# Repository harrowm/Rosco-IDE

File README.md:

# Rosco-IDE
A simple IDE interface for the rosco sbc based on the work of Mark Murray

This is arhcived .. the footprint for the ATF1508 is not correct .. do not attempt ot use!

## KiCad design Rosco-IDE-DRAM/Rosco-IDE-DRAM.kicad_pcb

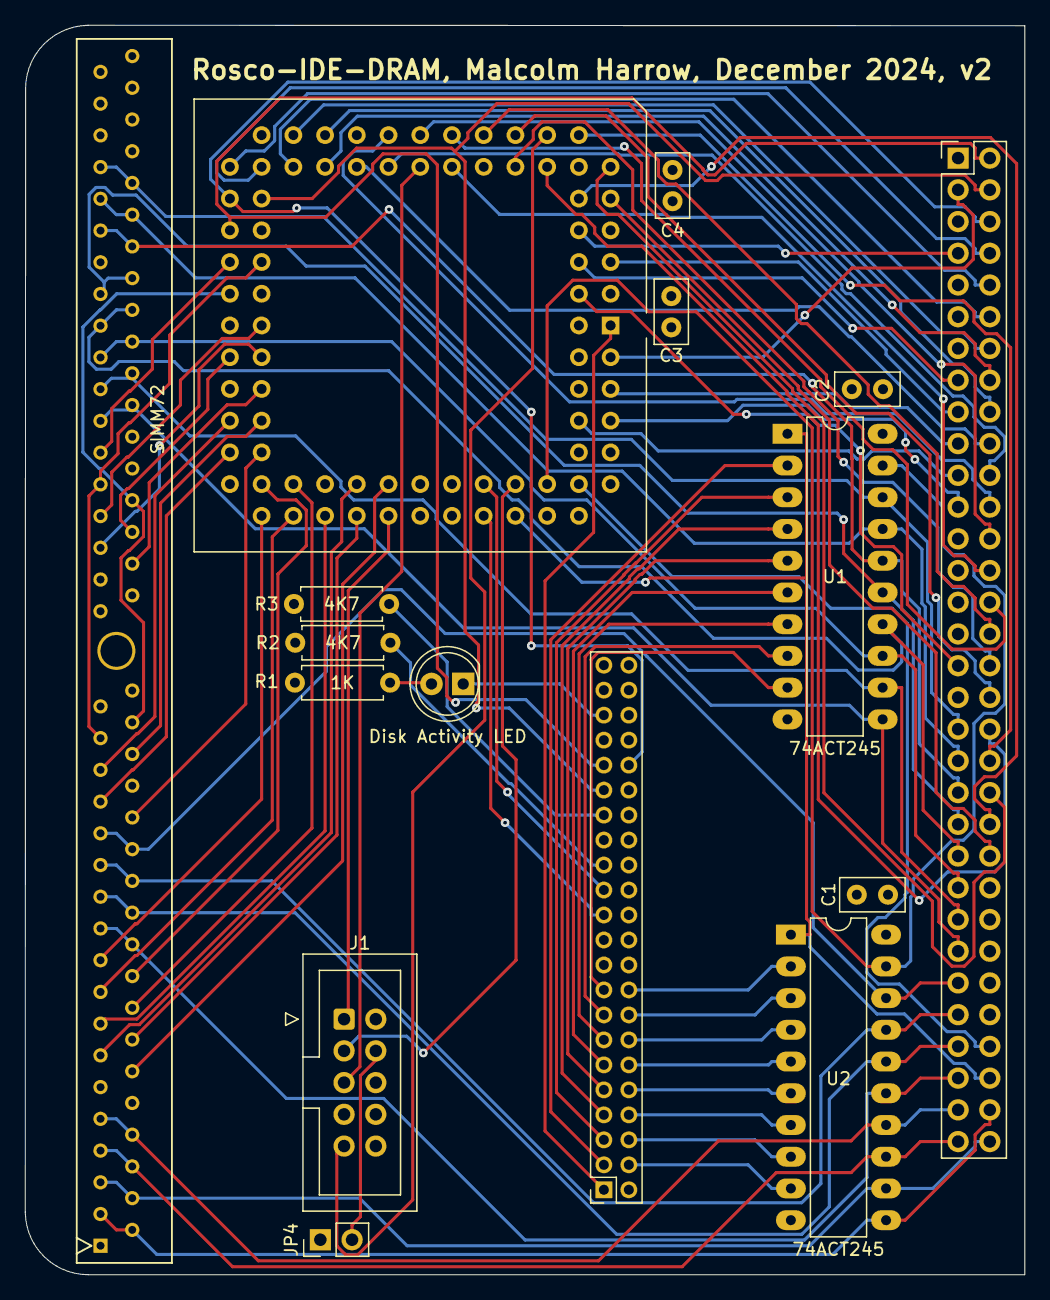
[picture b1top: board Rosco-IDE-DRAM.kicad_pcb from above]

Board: 4 copper layers, 80.0 x 100.0 mm, 16 parts (0 on the bottom side), 99 nets.

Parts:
BUS1: Conn_02x32_Odd_Even; PinHeader_2x32_P2.54mm_Vertical
C1, C2, C3, C4: 100nF; C_Disc_D5.0mm_W2.5mm_P2.50mm
D1: Disk Activity LED; LED_D5.0mm
J1: Conn_02x05_Odd_Even; IDC-Header_2x05_P2.54mm_Vertical
J2: Conn_02x22_Odd_Even; PinSocket_2x22_P2.00mm_Vertical
JP4: Jumper_2_Bridged; PinHeader_1x02_P2.54mm_Vertical
R1: 1K; R_Axial_DIN0207_L6.3mm_D2.5mm_P7.62mm_Horizontal
R2, R3: 4K7; R_Axial_DIN0207_L6.3mm_D2.5mm_P7.62mm_Horizontal
SIMM72: SIMM72
U1, U2: 74ACT245; DIP-20_W7.62mm_LongPads
U3: ATF1504; PLCC-84_THT-Socket

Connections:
+5V: BUS1.1, C1.1, C2.1, C3.1, C4.1, J2.41, JP4.1 (A), R1.1, SIMM72.10 (VCC), SIMM72.30 (VCC), SIMM72.59 (VCC), U1.20 (VCC), U2.20 (VCC), U3.3 (VCCINT), U3.13 (VCCIO), U3.26 (VCCIO), U3.38 (VCCIO), U3.43 (VCCINT), U3.53 (VCCIO), U3.66 (VCCIO), U3.78 (VCCIO)
A1: BUS1.2, J2.35, U3.37 (I/O)
A2: BUS1.4, J2.33, U3.36 (I/O)
A3: BUS1.6, J2.36, U3.35 (I/O)
A4: BUS1.8, U3.34 (I/O)
A5: BUS1.10, U3.33 (I/O)
A6: BUS1.12, U3.31 (I/O)
A7: BUS1.14, U3.30 (I/O)
A8: BUS1.16, U3.29 (I/O)
A9: BUS1.18, U3.28 (I/O)
A10: BUS1.20, U3.27 (I/O)
A11: BUS1.22, U3.25 (I/O)
A12: BUS1.24, U3.24 (I/O)
A13: BUS1.26, U3.22 (I/O)
A14: BUS1.28, U3.21 (I/O)
A15: BUS1.30, U3.20 (PD1/I/O)
A16: BUS1.32, U3.18 (I/O)
A17: BUS1.34, U3.17 (I/O)
A18: BUS1.36, U3.16 (I/O)
A19: BUS1.38, U3.15 (I/O)
A20: BUS1.40, U3.12 (I/O)
A21: BUS1.42, U3.11 (I/O)
A22: BUS1.44, U3.10 (I/O)
A23: BUS1.46, U3.9 (I/O)
BD0: J2.17, U1.9 (A7)
BD1: J2.15, U1.8 (A6)
BD2: J2.13, U1.7 (A5)
BD3: J2.11, U1.6 (A4)
BD4: J2.9, U1.5 (A3)
BD5: J2.7, U1.4 (A2)
BD6: J2.5, U1.3 (A1)
BD7: J2.3, U1.2 (A0)
BD8: J2.4, U2.9 (A7)
BD9: J2.6, U2.8 (A6)
BD10: J2.8, U2.7 (A5)
BD11: J2.10, U2.6 (A4)
BD12: J2.12, U2.5 (A3)
BD13: J2.14, U2.4 (A2)
BD14: J2.16, U2.3 (A1)
BD15: J2.18, U2.2 (A0)
CPUCLK: BUS1.3, U3.83 (GCLK1/I)
D0: BUS1.62, SIMM72.2 (DQ0), SIMM72.3 (DQ16), U2.11 (B7)
D1: BUS1.64, SIMM72.4 (DQ1), SIMM72.5 (DQ17), U2.12 (B6)
D2: BUS1.63, SIMM72.6 (DQ2), SIMM72.7 (DQ18), U2.13 (B5)
D3: BUS1.61, SIMM72.8 (DQ3), SIMM72.9 (DQ19), U2.14 (B4)
D4: BUS1.59, SIMM72.20 (DQ4), SIMM72.21 (DQ20), U2.15 (B3)
D5: BUS1.57, SIMM72.22 (DQ5), SIMM72.23 (DQ21), U2.16 (B2)
D6: BUS1.55, SIMM72.24 (DQ6), SIMM72.25 (DQ22), U2.17 (B1)
D7: BUS1.53, SIMM72.26 (DQ7), SIMM72.27 (DQ23), U2.18 (B0)
D8: BUS1.51, SIMM72.49 (DQ8), SIMM72.50 (DQ24), U1.11 (B7)
D9: BUS1.49, SIMM72.51 (DQ9), SIMM72.52 (DQ25), U1.12 (B6)
D10: BUS1.47, SIMM72.53 (DQ10), SIMM72.54 (DQ26), U1.13 (B5)
D11: BUS1.45, SIMM72.55 (DQ11), SIMM72.56 (DQ27), U1.14 (B4)
D12: BUS1.43, SIMM72.57 (DQ12), SIMM72.58 (DQ28), U1.15 (B3)
D13: BUS1.41, SIMM72.60 (DQ29), SIMM72.61 (DQ13), U1.16 (B2)
D14: BUS1.39, SIMM72.62 (DQ30), SIMM72.63 (DQ14), U1.17 (B1)
D15: BUS1.37, SIMM72.64 (DQ31), SIMM72.65 (DQ15), U1.18 (B0)
DTACK: BUS1.58, U3.76 (I/O)
EXPSEL: BUS1.17, U3.5 (I/O)
FC0: BUS1.19, U3.81 (GCLK3/I/O)
FC1: BUS1.21, U3.80 (I/O)
FC2: BUS1.23, U3.79 (I/O)
GND: BUS1.5, C1.2, C2.2, C3.2, C4.2, J1.2, J1.10, J2.2, J2.19, J2.22, J2.24, J2.26, J2.30, J2.40, J2.43, R2.2, R3.2, SIMM72.1 (GND), SIMM72.39 (GND), SIMM72.72 (GND), U1.10 (GND), U2.10 (GND), U3.7 (GND), U3.19 (GND), U3.32 (GND), U3.42 (GND), U3.47 (GND), U3.59 (GND), U3.72 (GND), U3.82 (GND)
IDEBUF: U1.19 (CE), U2.19 (CE), U3.73 (I/O)
INTRQ: J2.31, R3.1
IOSEL: BUS1.15, U3.6 (I/O)
MA0: SIMM72.12 (A0), U3.63 (I/O)
MA1: SIMM72.13 (A1), U3.61 (I/O)
MA2: SIMM72.14 (A2), U3.60 (I/O)
MA3: SIMM72.15 (A3), U3.58 (I/O)
MA4: SIMM72.16 (A4), U3.57 (I/O)
MA5: SIMM72.17 (A5), U3.56 (I/O)
MA6: SIMM72.18 (A6), U3.55 (I/O)
MA7: SIMM72.28 (A7), U3.52 (I/O)
MA8: SIMM72.31 (A8), U3.49 (I/O)
MA9: SIMM72.32 (A9), U3.50 (I/O)
MA10: SIMM72.19 (A10), U3.54 (I/O)
MA11: SIMM72.29 (A11), U3.51 (I/O)
unnamed: D1.2 (A), R1.2
unnamed: J1.4, JP4.2 (B)
unnamed: J2.27, R2.1
RW: BUS1.60, U1.1 (A->B), U2.1 (A->B), U3.70 (I/O)
TCK: J1.1, U3.62 (TCK/I/O)
TDI: J1.9, U3.14 (TDI/I/O)
TDO: J1.3, U3.71 (TDO/I/O)
TMS: J1.5, U3.23 (TMS/I/O)
UDS: BUS1.33, U3.4 (I/O)
VPA: BUS1.7, U3.8 (I/O)
~CAS0: SIMM72.40 (~CAS0), U3.48 (I/O)
~CAS1: SIMM72.43 (~CAS1), U3.44 (I/O)
~CAS2: SIMM72.41 (~CAS2), U3.46 (I/O/PD2)
~CAS3: SIMM72.42 (~CAS3), U3.45 (I/O)
~DASP: D1.1 (K), J2.39
~IDERD: J2.25, U3.69 (I/O)
~IDEWR: J2.23, U3.68 (I/O)
~MWE: SIMM72.47 (~WE), U3.39 (I/O)
~RAS0: SIMM72.34 (~RAS2), SIMM72.44 (~RAS0), U3.41 (I/O)
~RAS1: SIMM72.33 (~RAS3), SIMM72.45 (~RAS1), U3.40 (I/O)
~RESET: J2.1, U3.1 (GCLR/I)

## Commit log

2024-04-30 Added 72 pin SIMM
2025-03-14 Mothballing
